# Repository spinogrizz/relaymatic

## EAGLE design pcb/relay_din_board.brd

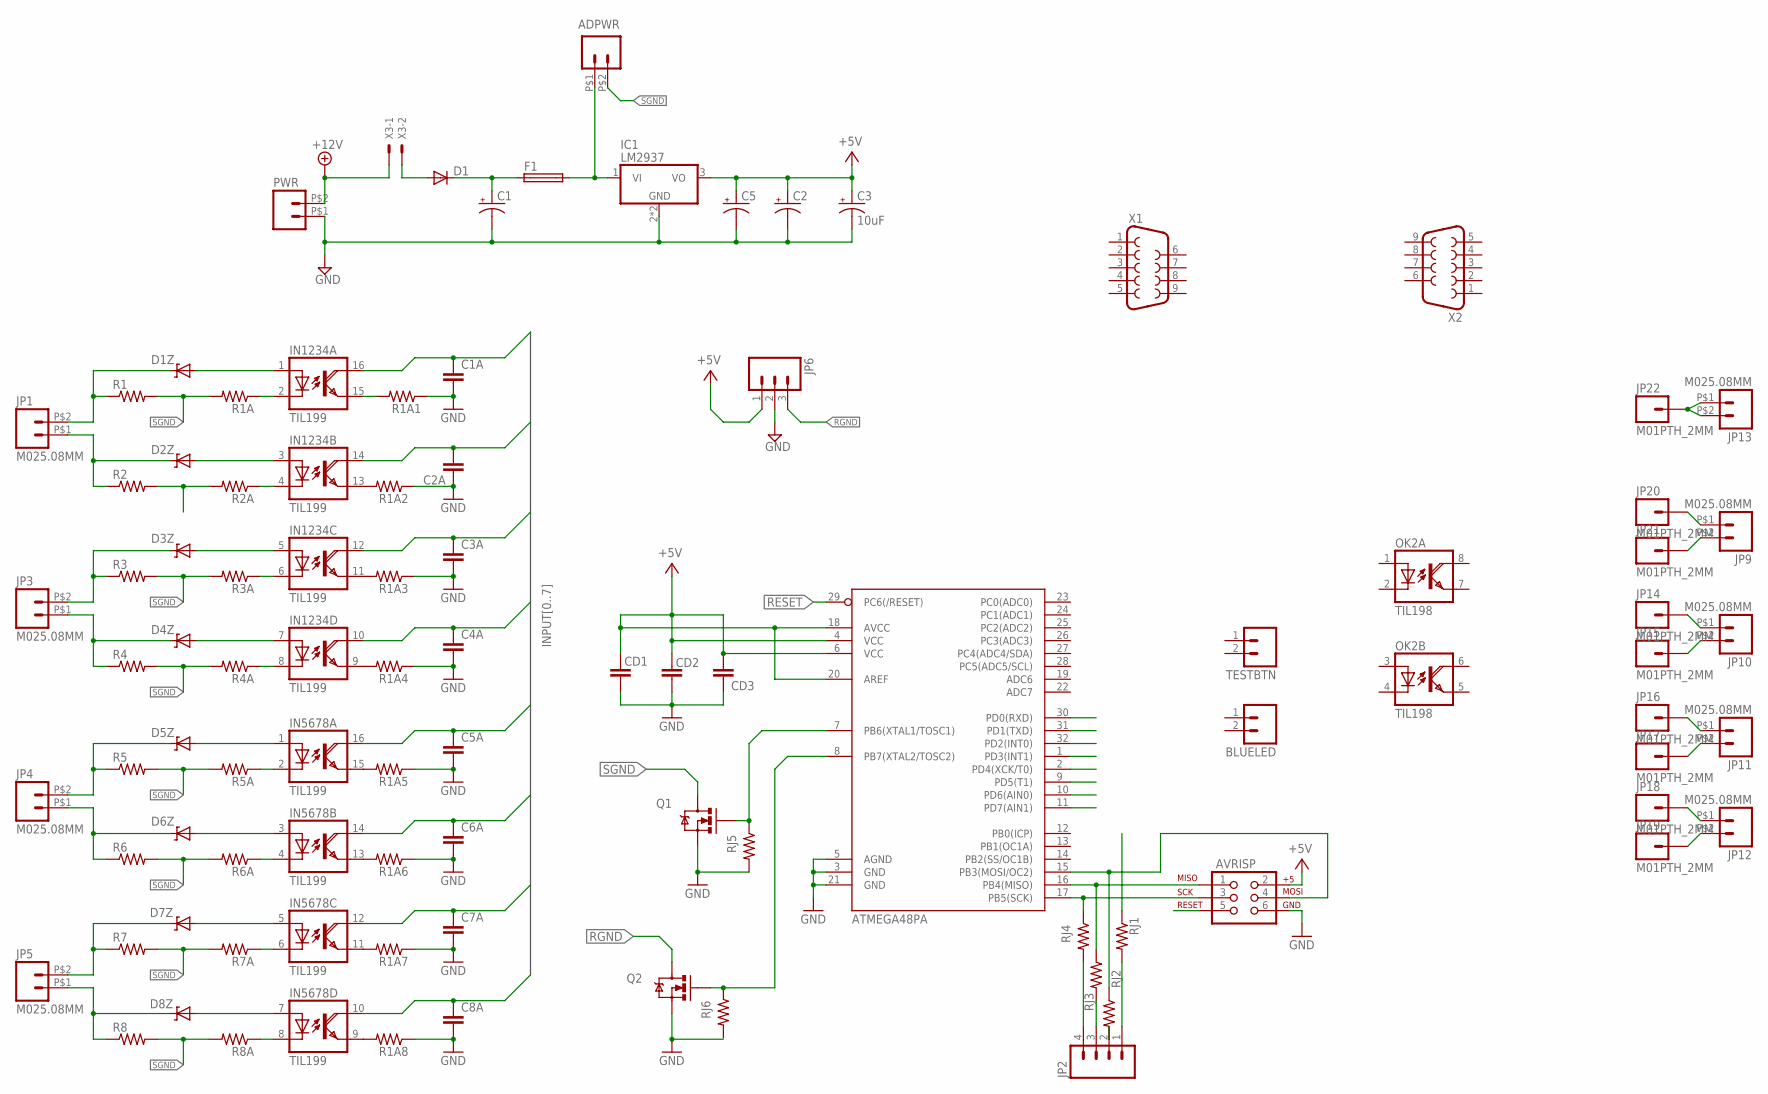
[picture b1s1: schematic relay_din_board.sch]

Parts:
ADPWR: M025.08MM; SCREWTERMINAL-5.08MM-2
ATMEGA48PA: ATMEGA168; TQFP32-08
AVRISP: AVR_SPI_PRG_6PTH; 2X3
BLUELED: M02PTH; 1X02
C1: CPOL-USE5-10.5; E5-10,5
C1A, C2A, C3A, C4A, C5A, C6A, C7A, C8A: CAP0805; 0805
C2, C5: CPOL-US153CLV-0605; 153CLV-0605
C3: 10uF; EIA3216
CD1, CD2, CD3: CAP0805; 0805
D1: DIODE-C1702-05; C1702-05
D1Z, D2Z, D3Z, D4Z, D5Z, D6Z, D7Z, D8Z: DIODE-ZENER-BZT52; SOD-323
F1: GSH15
IC1: LM2937; TO263-3
IN1234, IN5678: TIL199; DIL16
JP1, JP3, JP4, JP5, JP9, JP10, JP11, JP12, JP13: M025.08MM; SCREWTERMINAL-5.08MM-2
JP2: M04PTH; 1X04
JP6: M03PTH; 1X03
JP14, JP15, JP16, JP17, JP18, JP19, JP20, JP21, JP22: M01PTH_2MM; 1X01_2MM
OK2: TIL198; DIL08
PWR: M025.08MM; SCREWTERMINAL-5.08MM-2
Q1, Q2: MOSFET-NCHANNELBSS123LT1G; SOT23
R1, R2, R3, R4, R5, R6, R7, R8: RESISTOR2512; R2512
R1A, R1A1, R1A2, R1A3, R1A4, R1A5, R1A6, R1A7, R1A8, R2A, R3A, R4A, R5A, R6A, R7A, R8A: RESISTOR0805-RES; 0805
RJ1, RJ2, RJ3, RJ4, RJ5, RJ6: RESISTOR0805-RES; 0805
TESTBTN: M02PTH; 1X02
X1: DB9FEMALE; DB9
X2: DB9MALE; DB9_MALE
X3: 22-23-2021

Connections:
+5V: ATMEGA48PA.4 (VCC), ATMEGA48PA.6 (VCC), ATMEGA48PA.18 (AVCC), ATMEGA48PA.20 (AREF), AVRISP.2, C2.+, C3.A (+), C5.+, CD1.1, CD2.1, CD3.1, IC1.3 (VO), JP6.1
+12V: PWR.P$2 (2), X3.1
GND: ATMEGA48PA.3 (GND), ATMEGA48PA.5 (AGND), ATMEGA48PA.21 (GND), AVRISP.6, C1.-, C1A.2, C2.-, C2A.1, C3.C (-), C3A.2, C4A.2, C5.-, C5A.2, C6A.2, C7A.2, C8A.2, CD1.2, CD2.2, CD3.2, IC1.2 (GND), IC1.TAB (GND), JP6.2, PWR.P$1 (1), Q1.2 (S), Q2.2 (S), R1A1.1, R1A2.1, R1A3.1, R1A4.1, R1A5.1, R1A6.1, R1A7.1, R1A8.1, RJ5.2
INPUT0: ATMEGA48PA.30 (PD0(RXD)), C1A.1, IN1234.16 (COL)
INPUT1: ATMEGA48PA.31 (PD1(TXD)), C2A.2, IN1234.14 (COL)
INPUT2: ATMEGA48PA.32 (PD2(INT0)), C3A.1, IN1234.12 (COL)
INPUT3: ATMEGA48PA.1 (PD3(INT1)), C4A.1, IN1234.10 (COL)
INPUT4: ATMEGA48PA.2 (PD4(XCK/T0)), C5A.1, IN5678.16 (COL)
INPUT5: ATMEGA48PA.9 (PD5(T1)), C6A.1, IN5678.14 (COL)
INPUT6: ATMEGA48PA.10 (PD6(AIN0)), C7A.1, IN5678.12 (COL)
INPUT7: ATMEGA48PA.11 (PD7(AIN1)), C8A.1, IN5678.10 (COL)
unnamed: IN1234.15 (EMI), R1A1.2
unnamed: IN1234.13 (EMI), R1A2.2
unnamed: ATMEGA48PA.17 (PB5(SCK)), AVRISP.3, RJ4.1
unnamed: ATMEGA48PA.16 (PB4(MISO)), AVRISP.1, RJ3.1
unnamed: IN1234.11 (EMI), R1A3.2
unnamed: IN1234.9 (EMI), R1A4.2
unnamed: IN5678.15 (EMI), R1A5.2
unnamed: IN5678.13 (EMI), R1A6.2
unnamed: IN5678.11 (EMI), R1A7.2
unnamed: IN5678.9 (EMI), R1A8.2
unnamed: JP2.4, RJ4.2
unnamed: JP2.3, RJ3.2
unnamed: D1Z.1 (C), JP1.P$2 (2), R1.1
unnamed: D2Z.1 (C), JP1.P$1 (1), R2.1
unnamed: IN1234.2 (C), R1A.1
unnamed: D1Z.2 (A), IN1234.1 (A)
unnamed: D2Z.2 (A), IN1234.3 (A)
unnamed: IN1234.4 (C), R2A.1
unnamed: D4Z.1 (C), JP3.P$1 (1), R4.1
unnamed: D3Z.1 (C), JP3.P$2 (2), R3.1
unnamed: D5Z.1 (C), JP4.P$2 (2), R5.1
unnamed: D5Z.2 (A), IN5678.1 (A)
unnamed: IN1234.6 (C), R3A.1
unnamed: IN5678.6 (C), R7A.1
unnamed: D4Z.2 (A), IN1234.7 (A)
unnamed: IN1234.8 (C), R4A.1
unnamed: JP2.2, RJ2.2
unnamed: IN5678.2 (C), R5A.1
unnamed: ADPWR.P$1 (1), F1.2, IC1.1 (VI)
unnamed: D6Z.2 (A), IN5678.3 (A)
unnamed: IN5678.4 (C), R6A.1
unnamed: D6Z.1 (C), JP4.P$1 (1), R6.1
unnamed: D7Z.1 (C), JP5.P$2 (2), R7.1
unnamed: D8Z.1 (C), JP5.P$1 (1), R8.1
unnamed: D3Z.2 (A), IN1234.5 (A)
unnamed: D8Z.2 (A), IN5678.7 (A)
unnamed: IN5678.8 (C), R8A.1
unnamed: D7Z.2 (A), IN5678.5 (A)
unnamed: JP2.1, RJ1.2
unnamed: ATMEGA48PA.15 (PB3(MOSI/OC2)), AVRISP.4, RJ2.1
unnamed: C1.+, D1.C, F1.1
unnamed: D1.A, X3.2
unnamed: JP10.P$1 (1), JP14.1
unnamed: ATMEGA48PA.7 (PB6(XTAL1/TOSC1)), Q1.1 (G), RJ5.1
unnamed: JP10.P$2 (2), JP15.1
unnamed: JP11.P$1 (1), JP16.1
unnamed: JP12.P$1 (1), JP18.1
unnamed: JP12.P$2 (2), JP19.1
unnamed: JP11.P$2 (2), JP17.1
unnamed: JP9.P$1 (1), JP20.1
unnamed: JP9.P$2 (2), JP21.1
unnamed: JP13.P$1 (1), JP13.P$2 (2), JP22.1
unnamed: ATMEGA48PA.8 (PB7(XTAL2/TOSC2)), Q2.1 (G), RJ6.1
RESET: ATMEGA48PA.29 (PC6(/RESET)), AVRISP.5
RGND: JP6.3, Q2.3 (D)
SGND: ADPWR.P$2 (2), Q1.3 (D), R1.2, R1A.2, R2.2, R2A.2, R3.2, R3A.2, R4.2, R4A.2, R5.2, R5A.2, R6.2, R6A.2, R7.2, R7A.2, R8.2, R8A.2

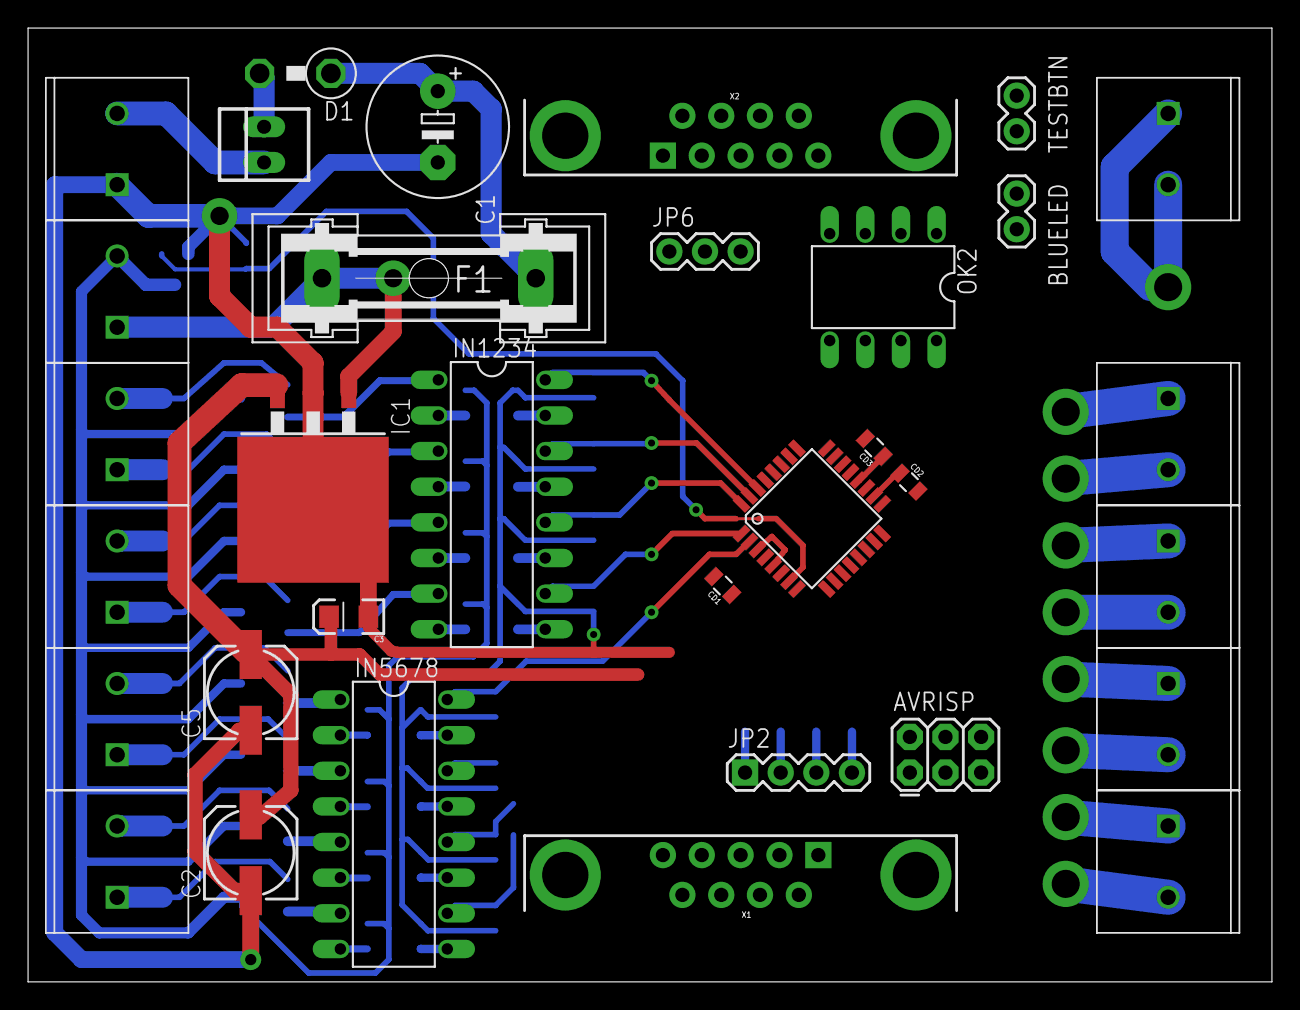
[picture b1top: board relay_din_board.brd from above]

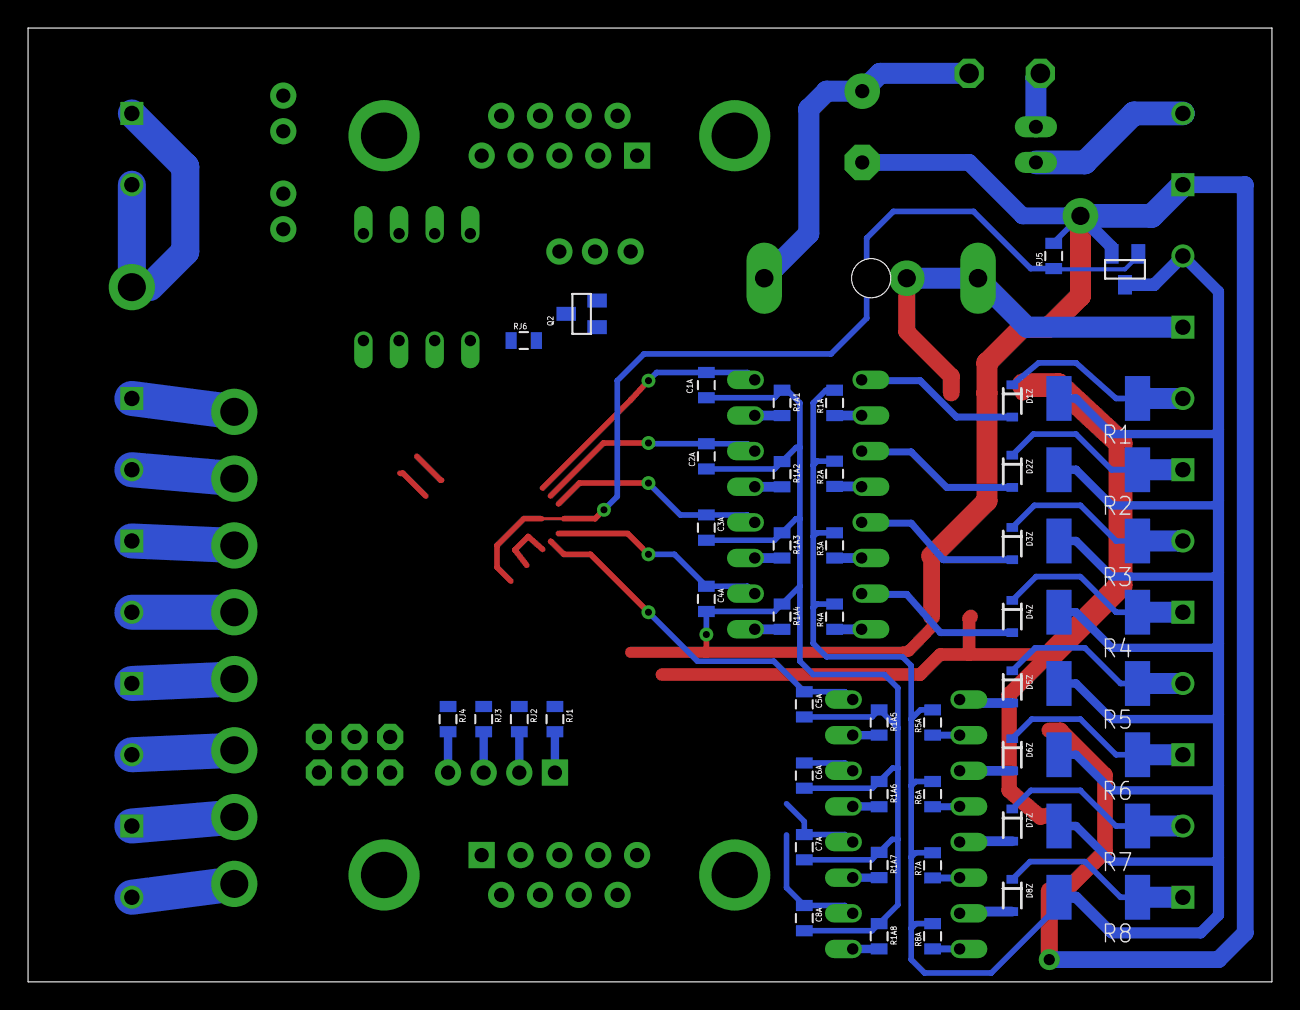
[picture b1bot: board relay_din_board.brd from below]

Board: 2 copper layers, 88.7 x 68.0 mm, 90 parts (48 on the bottom side), 67 nets.

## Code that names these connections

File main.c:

#include <avr/io.h>
#include <util/delay.h>
#include <avr/interrupt.h>
#include <stdlib.h> 
#include <stdbool.h> 
#include <avr/sleep.h>
#include <avr/wdt.h>
#include <avr/eeprom.h> 

#include "input.h"
#include "output.h"
#include "i2c.h"
#include "interface.h"

#define DEVICE_CLASS  0x0E

#define POWER_SWITCHES    (1<<PB6)
#define POWER_RELAYS    (1<<PB7)

#define LONG_TIME_RESET_INTERVAL    3600  //reset switches every hours
#define EEPROM_SAVE_MIN_TIMEOUT     15    //schedule EEPROM save only once in 15 seconds

#define DEBUG_MODE 0

#if DEBUG_MODE
    #define DEBUG1 (1<<PD6)
    #define DEBUG2 (1<<PD7)
#endif

#define REMOTE_COMMAND_LED (1<<PC2)

uint8_t storedOutputValues[8] EEMEM = { 0x00 };
volatile bool outputStateNeedsToBeSaved = false;

uint8_t i2c_address_num EEMEM = (DEVICE_CLASS<<3);

enum RemoteCommands {
    //set commands
    Command_SetPortValue = 's',  //lsb 4 bits — port number, msb 4 bits — 0x1111 = on, 0x0000 = off
    Command_SetAllPortBits = 'S', //use bit mask to toggle all ports
    Command_TogglePortValue = 't', 
    Command_AllSwitchOff = 'f',
    Command_AllSwitchOn = 'n',

    //get commands
    Command_GetPortValue = 'g',  //return port by number
    Command_GetAllPortBits = 'G'  //return ports bit mask
};

void init_ports() {
    //default values
    PCMSK0 = 0x00; PCMSK1 = 0x00; PCMSK2 = 0x00;
    PCICR = 0x00;

    init_input_ports();
    init_output_ports();
    init_interface_ports();

#if DEBUG_MODE
    //debug leds
    DDRD |= (DEBUG1|DEBUG2);
    PORTD &= ~(DEBUG1|DEBUG2);
#endif

    //external 12v switch power control, and 5v for relays
    DDRB |= (POWER_SWITCHES|POWER_RELAYS);
    PORTB &= ~(POWER_SWITCHES|POWER_RELAYS);

    //blue led indicator
    DDRC |= (REMOTE_COMMAND_LED);
    PORTC &= ~(REMOTE_COMMAND_LED);

    //interrupt line
    DDRC |= (INTERRUPT_LINE);    
    PORTC &= ~(INTERRUPT_LINE); 
}

void input_trigger(uint8_t number) {
    uint8_t currentMask = currentOutputStateMask();
    currentMask ^= _BV(number); //toggle by default
    setOutputStateMask(currentMask);
    outputStateNeedsToBeSaved = true; //schedule eeprom save

    iface_controlInterruptLine(true); //trigger interrupt line to report to the master
}

//i2c write commands
void i2c_executeWriteCommand(char command, uint8_t data) {
    uint8_t mask = currentOutputStateMask();

    switch (command) {
        case Command_SetPortValue: {
            //lsb 4 bits — port number
            //msb 4 bits — 0x1111 = on, 0x0000 = off
            uint8_t port = (data & 0x0F);
            uint8_t value = ((data & 0xF0)>>4);

            if ( value != 0x00 ) {
                mask |= _BV(port-1);
            } else {
                mask &= ~_BV(port-1);
            }
            break;
        }
        case Command_TogglePortValue:
            mask ^= (1<<(data-1)); //toggle on bit
            break;
        case Command_SetAllPortBits:
            mask = data;
            break;
        case Command_AllSwitchOn:
            mask = 0xFF;
            break;
        case Command_AllSwitchOff:
            mask = 0x00;
            break;
        default:
            break;
    }

    setOutputStateMask(mask);
    outputStateNeedsToBeSaved = true;

    PORTC |= REMOTE_COMMAND_LED; //blink blue led
}

//i2c read commands
void i2c_executeReadCommand(char command, uint8_t argument, volatile uint8_t *outputData) {
    uint8_t mask = currentOutputStateMask();

    switch (command) {
        case Command_GetPortValue:
            if ( (mask & _BV(argument)) != 0 ) {
                *outputData = 0xFF;
            } else {
                *outputData = 0x00;
            }
            break;
        case Command_GetAllPortBits:
            *outputData = mask;
            break;
        default: 
            *outputData = 0x00;
            break;
    }

    //master received our new state, release the interrupt line
    iface_controlInterruptLine(false);    
}

void iface_receivedAddressNumber(uint8_t address) {
    //lsb 3 bits — device number
    //next 4 bits — device class
    uint8_t classPart = (DEVICE_CLASS&0xF) << 3;
    uint8_t addressPart = address & 0x7;
    uint8_t newAddress = (classPart | addressPart);

    //restart i2c with a new address
    init_i2c(newAddress);

    //store that address in eeprom
    eeprom_write_byte((uint8_t *)&i2c_address_num, newAddress);
}

//slowly turn power to switches and relays
void delayed_power_sequence() {
    cli(); {
        _delay_ms(10);

        PORTB &= ~POWER_SWITCHES;
        PORTB &= ~POWER_RELAYS;
        _delay_ms(50);

        PORTB |= POWER_SWITCHES;
        _delay_ms(50);

        PORTB |= POWER_RELAYS;    
        _delay_ms(50);
    }; sei();
}

//the values in EEPROM are spread in 8 bytes, probably for a better data retention
void eeprom_restore_state_mask() {
    uint8_t outputValues[8] = { 0 };
    uint8_t newMask = 0x00;
    eeprom_read_block((uint8_t *)outputValues, (const uint8_t *)storedOutputValues, 8);

    for ( int i=0; i<8; i++ ) {
        newMask |= outputValues[i] ? _BV(i) : 0;
    }

    setOutputStateMaskSlowly(newMask);
}

void eeprom_save_state_mask() {
    uint8_t outputValues[8] = { 0 };
    uint8_t currentMask = currentOutputStateMask();

    for ( int i=0; i<8; i++ ) {
        outputValues[i] = ((currentMask & _BV(i)) != 0) ? 0xFF : 0x00;
    }

    eeprom_write_block((const uint8_t *)outputValues, (uint8_t *)storedOutputValues, 8);
}

//use slow 16-bit timer to measure 5 seconds intervals and trigger several timeouts
void init_timeout_timer() {
    TCCR1A = 0x00;
    TCCR1B = _BV(WGM12) | _BV(CS10) | _BV(CS12); //1024 prescaler, CTC mode

    OCR1A = 5*F_CPU/1024; //each 5 seconds

    TIMSK1 = _BV(OCIE1A); //overflow interrupt enabled
    TIFR1 &= ~_BV(OCF1A); //reset flag
} 

//these flags indicates if whether there are new actions to be done
volatile bool needsLongTimeReset = false;
volatile bool needsEepromSave = false;

void each_5_seconds() { 
    static uint16_t longTimeResetCnt = 0x00;
    static uint8_t eepromWriteTimeout = 0x00;   

    if ( ++longTimeResetCnt == LONG_TIME_RESET_INTERVAL/5 ) {
        needsLongTimeReset = true;
        longTimeResetCnt = 0;
    }

    if ( ++eepromWriteTimeout == EEPROM_SAVE_MIN_TIMEOUT/5 ) { 
        needsEepromSave = outputStateNeedsToBeSaved;
        eepromWriteTimeout = 0;
    }
}

ISR(TIMER1_COMPA_vect) {
    each_5_seconds();
}

int main() {
    MCUSR &= ~_BV(WDRF); //clear watchdog reset flag     
    wdt_disable(); //disable watchdog

    cli(); {
        //init PORTs, DDRs and PINs
        init_ports();

        //init periodic timer
        init_timeout_timer();

        //slowly turn power to relays and switches
        delayed_power_sequence();

        //reload stored values from eeprom
        eeprom_restore_state_mask();

        //declare i2c read commands
        char readCommands[] = {Command_GetPortValue, Command_GetAllPortBits};
        i2c_setReadCommands(readCommands , 2);

        //restore i2c address from eeprom
        uint8_t i2c_address = eeprom_read_byte((uint8_t *)&i2c_address_num);
        i2c_address &= 0x7F; //mask out one msb
        init_i2c(i2c_address);
    }; sei();

    //main loop
    while(1) {
        wdt_reset();

        //everyone has their time on the loop
        process_input();
        process_i2c();
        process_output();
        process_interface();

        //wait before going to sleep
        _delay_ms(5);

        if ( i2c_commandsAvailable() || output_hasNewState() ) {
            continue; //skip sleep mode, repeat all processes
        }

        //do we have a new values state?
        if ( needsEepromSave ) {
            eeprom_save_state_mask();
            needsEepromSave = false;
        }

        //reset everything each hour, allowing touch switches to recalibrate
        if ( needsLongTimeReset ) {
            cli(); {
                PORTB &= ~POWER_SWITCHES;
                _delay_ms(800);
                PORTB |= POWER_SWITCHES;
                _delay_ms(100);

                needsLongTimeReset = false;
            }; sei();
        }

        //turn off blue led
        PORTC &= ~(REMOTE_COMMAND_LED);

#if DEBUG_MODE
        PORTD &= ~(DEBUG1|DEBUG2);
#endif

        //do not let watchdog reset us during sleep
        wdt_disable();

        //nothing to do, go to idle sleep
        set_sleep_mode(SLEEP_MODE_IDLE);
        sleep_enable();
        sleep_cpu();

        wdt_enable(WDTO_1S); //restore watchdog timer
    }

    return 0;  
}

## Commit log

2013-10-20 initial work commit
2013-10-20 fix whitespace
2013-10-20 fix i2c, main loop queue issues
2013-10-26 i2c queue
2013-10-26 watchdog reset
2013-10-26 i2c state machine (not finished)
2013-10-27 fixes i2c queue
2013-10-27 all external commands
2013-10-27 save state to eeprom, timeout timer
2013-10-27 switched to 16-bit timer
2013-11-02 interrupt line
2013-11-02 finished i2c auto addressing, new tests
2013-11-02 some documentation (work in progress)
2013-11-03 store i2c address in eeprom
2013-11-03 all code commented
2013-11-17 added schematic and board (Eagle)

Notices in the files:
parts and their libraries:
SparkFun-Connectors: Licensing: CC v3.0 Share-Alike You are welcome to use this library for commercial purposes.
